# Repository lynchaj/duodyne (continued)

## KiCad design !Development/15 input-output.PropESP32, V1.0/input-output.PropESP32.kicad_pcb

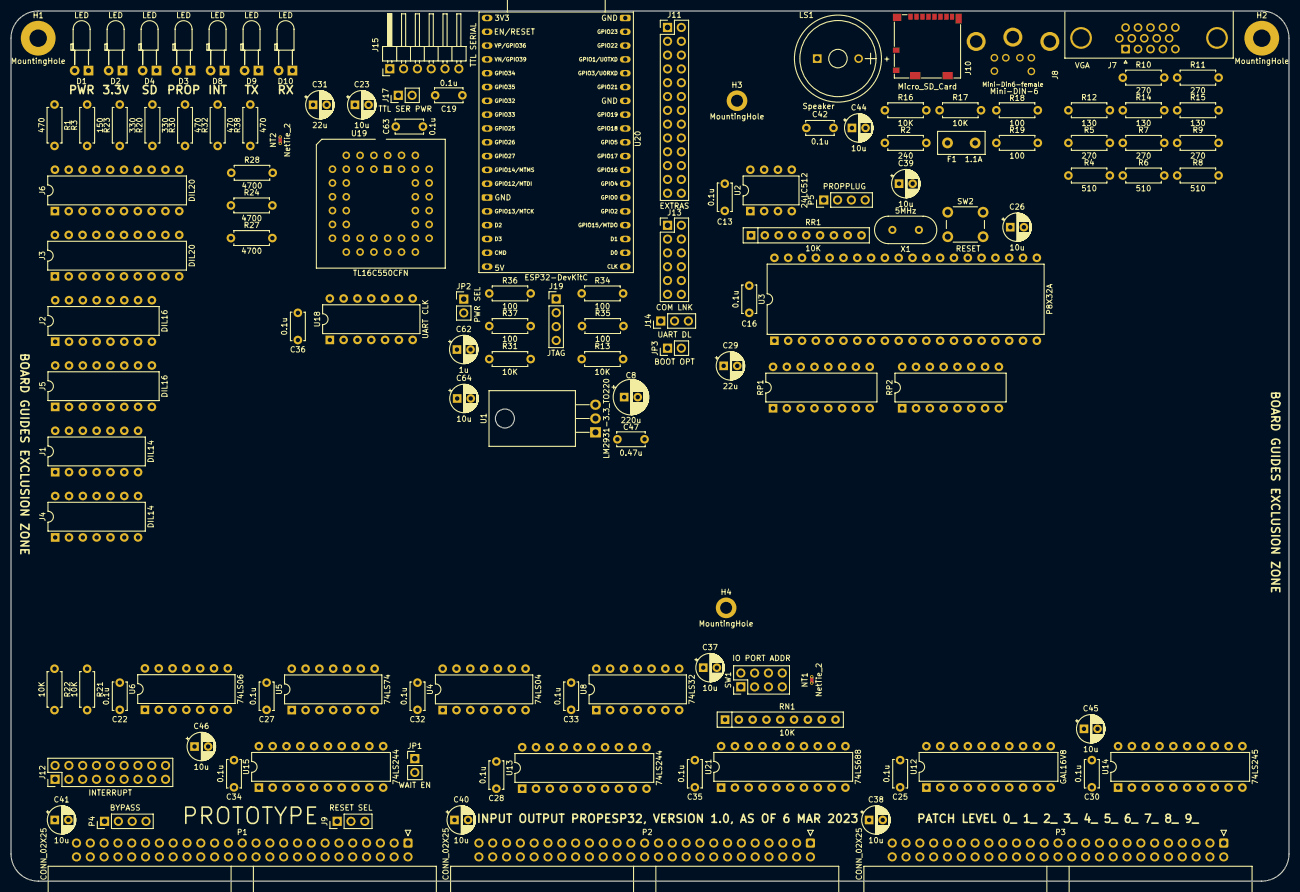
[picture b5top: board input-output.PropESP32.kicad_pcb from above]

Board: 2 copper layers, 235.0 x 160.0 mm, 127 parts (0 on the bottom side), 192 nets, no tracks yet.

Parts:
C8: 220u; CP_Radial_D6.3mm_P2.50mm
C13, C16, C19, C22, C25, C27, C28, C30, C32, C33, C34, C35, C36, C42, C63: 0.1u; C_Disc_D5.0mm_W2.5mm_P5.00mm
C23, C26, C37, C38, C39, C40, C41, C44, C45, C46, C64: 10u; CP_Radial_D5.0mm_P2.50mm
C29, C31: 22u; CP_Radial_D5.0mm_P2.50mm
C47: 0.47u; C_Disc_D5.0mm_W2.5mm_P5.00mm
C62: 1u; CP_Radial_D5.0mm_P2.50mm
D1, D2, D3, D4, D8, D9, D10: LED; LED_D3.0mm_Horizontal_O3.81mm_Z2.0mm
F1: 1.1A; Fuse_Littelfuse_395Series
H1, H2: MountingHole; MountingHole_3.2mm_M3_Pad
H3, H4: MountingHole; MountingHole_2.2mm_M2_DIN965_Pad
J1, J4: DIL14; DIP-14_W7.62mm
J2, J5: DIL16; DIP-16_W7.62mm
J3, J6: DIL20; DIP-20_W7.62mm
J7: VGA; DSUB-15-HD_Female_Horizontal_P2.29x1.98mm_EdgePinOffset3.03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
J8: Mini-DIN-6; mini-din6-female
J9: RESET SEL; PinHeader_1x03_P2.54mm_Vertical
J10: Micro_SD_Card; microSD_HC_Molex_104031-0811
J11: EXTRAS; PinHeader_2x13_P2.54mm_Vertical
J12: INTERRUPT; PinHeader_2x09_P2.54mm_Vertical
J13: COM LNK; PinHeader_2x06_P2.54mm_Vertical
J14: UART DL; PinHeader_1x03_P2.54mm_Vertical
J15: TTL SERIAL; PinHeader_1x06_P2.54mm_Horizontal
J17: TTL SER PWR; PinHeader_1x02_P2.54mm_Vertical
J19: JTAG; PinHeader_1x04_P2.54mm_Vertical
JP1: WAIT EN; PinHeader_1x02_P2.54mm_Vertical
JP2: PWR SEL; PinHeader_1x02_P2.54mm_Vertical
JP3: BOOT OPT; PinHeader_1x02_P2.54mm_Vertical
LS1: Speaker; MagneticBuzzer_StarMicronics_HMB-06_HMB-12
NT1, NT2: NetTie_2; NetTie-2_THT_Pad0.3mm
P1, P2, P3: CONN_02X25; IDC-Header_2x25_P2.54mm_Horizontal
P4: BYPASS; PinHeader_1x04_P2.54mm_Vertical
P5: PROPPLUG; PinHeader_1x04_P2.54mm_Vertical
R1, R30, R32, R38: 470; R_Axial_DIN0207_L6.3mm_D2.5mm_P7.62mm_Horizontal
R2: 240; R_Axial_DIN0207_L6.3mm_D2.5mm_P7.62mm_Horizontal
R3: 150; R_Axial_DIN0207_L6.3mm_D2.5mm_P7.62mm_Horizontal
R4, R6, R8: 510; R_Axial_DIN0207_L6.3mm_D2.5mm_P7.62mm_Horizontal
R5, R7, R9, R10, R11: 270; R_Axial_DIN0207_L6.3mm_D2.5mm_P7.62mm_Horizontal
R12, R14, R15: 130; R_Axial_DIN0207_L6.3mm_D2.5mm_P7.62mm_Horizontal
R13, R16, R17, R21, R22, R31: 10K; R_Axial_DIN0207_L6.3mm_D2.5mm_P7.62mm_Horizontal
R18, R19, R34, R35, R36, R37: 100; R_Axial_DIN0207_L6.3mm_D2.5mm_P7.62mm_Horizontal
R20, R23: 330; R_Axial_DIN0207_L6.3mm_D2.5mm_P7.62mm_Horizontal
R24, R27, R28: 4700; R_Axial_DIN0207_L6.3mm_D2.5mm_P7.62mm_Horizontal
RN1: 10K; R_Array_SIP9
RP1, RP2: 4700; DIP-16_W7.62mm
RR1: 10K; R_Array_SIP9
SW1: IO PORT ADDR; PinHeader_2x04_P2.54mm_Vertical
SW2: RESET; SW_PUSH_6mm
U1: LM2931-3.3_TO220; TO-220-3_Horizontal_TabDown
U2: 24LC512; DIP-8_W7.62mm
U3: P8X32A; DIP-40_W15.24mm
U4: 74LS04; DIP-14_W7.62mm
U5: 74LS74; DIP-14_W7.62mm
U6: 74LS06; DIP-14_W7.62mm
U8: 74LS32; DIP-14_W7.62mm
U12: GAL16V8; DIP-20_W7.62mm
U13, U15: 74LS244; DIP-20_W7.62mm
U14: 74LS245; DIP-20_W7.62mm
U18: UART CLK; DIP-14_W7.62mm
U19: TL16C550CFN; PLCC-44_THT-Socket
U20: ESP32-DevKitC
U21: 74LS688; DIP-20_W7.62mm
X1: 5MHz; Crystal_HC49-4H_Vertical

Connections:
+12V: P2.19, P2.20
-12V: P2.37, P2.38
/ESP32/CLK-ESP32: J11.22, U20.20 (SD_CLK/GPIO6)
/ESP32/CLK_UART: U18.8, U18.11, U19.18 (XIN)
/ESP32/CMD: J11.24, U20.18 (CMD)
/ESP32/EN: C62.1, R31.1, U20.2 (CHIP_PU)
/ESP32/INT: U6.9, U6.11, U19.33 (INTR)
/ESP32/IO0: JP3.1 (A), U20.25 (*GPIO0/BOOT/ADC2_CH1)
/ESP32/IO2: J11.16, U20.24 (ADC2_CH2/*GPIO2)
/ESP32/IO4: J13.2, U20.26 (ADC2_CH0/GPIO4)
/ESP32/IO5: J13.4, U20.29 (*GPIO5)
/ESP32/IO16: J11.14, U20.27 (GPIO16)
/ESP32/IO17: J11.12, U20.28 (GPIO17)
/ESP32/IO18: J13.6, U20.30 (GPIO18)
/ESP32/IO19: J13.8, U20.31 (GPIO19)
/ESP32/IO21: J11.8, U20.33 (GPIO21)
/ESP32/IO22: J11.6, U20.36 (GPIO22)
/ESP32/IO23: J11.4, U20.37 (GPIO23)
/ESP32/IO25: J11.15, U20.9 (DAC_1/ADC2_CH8/GPIO25)
/ESP32/IO26: J11.17, U20.10 (DAC_2/ADC2_CH9/GPIO26)
/ESP32/IO27: J11.19, U20.11 (ADC2_CH7/GPIO27)
/ESP32/IO32: J11.11, U20.7 (32K_XP/GPIO32/ADC1_CH4)
/ESP32/IO33: J11.13, U20.8 (32K_XN/GPIO33/ADC1_CH5)
/ESP32/IO34: J11.7, U20.5 (VDET_1/GPIO34/ADC1_CH6)
/ESP32/IO35: J11.9, U20.6 (VDET_2/GPIO35/ADC1_CH7)
/ESP32/MTCK: R37.1, U20.15 (MTCK/GPIO13/ADC2_CH4)
/ESP32/MTDI: R34.1, U20.13 (*MTDI/GPIO12/ADC2_CH5)
/ESP32/MTDO: R35.1, U20.23 (*MTDO/GPIO15/ADC2_CH3)
/ESP32/MTMS: R36.1, U20.12 (MTMS/GPIO14/ADC2_CH6)
/ESP32/RXD: J13.12, J14.2, U20.34 (U0RXD/GPIO3)
/ESP32/SD0: J11.20, U20.21 (SD_DATA0/GPIO7)
/ESP32/SD1: J11.18, U20.22 (SD_DATA1/GPIO8)
/ESP32/SD2: J11.23, U20.16 (SD_DATA2/GPIO9)
/ESP32/SD3: J11.25, U20.17 (SD_DATA3/GPIO10)
/ESP32/SENSOR_VN: J11.5, U20.4 (SENSOR_VN/GPIO39/ADC1_CH3)
/ESP32/SENSOR_VP: J11.3, U20.3 (SENSOR_VP/GPIO36/ADC1_CH0)
/ESP32/TTL_CTS#: J13.5, J15.6, U19.40 (~CTS)
/ESP32/TTL_RTS#: J13.7, J15.2, U19.36 (~RTS)
/ESP32/TTL_RX: J13.1, J13.9, J15.4, U8.12, U8.13, U19.11 (SIN)
/ESP32/TTL_TX: J13.3, J13.11, J15.5, U8.9, U8.10, U19.13 (SOUT)
/ESP32/TXD: J13.10, J14.3, U20.35 (U0TXD/GPIO1)
/ESP32/VCC_ESP32: JP2.2 (B), U20.19 (5V)
/ESP32/bRESET: R28.1, U4.8
/ESP32/pRESET: R28.2, U19.39 (MR)
/Propeller/BLUE: J7.3, R8.2, R9.2, R15.2
/Propeller/CLR: R13.2, U3.17 (P12), U4.3
/Propeller/DAT2: J10.1 (DAT2), R17.2
/Propeller/DI/CMD: J10.3 (CMD), RR1.5 (R4), U3.35 (P26)
/Propeller/DO/DAT0: J10.7 (DAT0), RR1.7 (R6), U3.33 (P24)
/Propeller/GREEN: J7.2, R6.2, R7.2, R14.2
/Propeller/HSYNC: J7.13, R10.2
/Propeller/KBD_CLK: R19.1, RR1.9 (R8), U3.20 (P15)
/Propeller/KBD_DAT: R18.1, RR1.8 (R7), U3.19 (P14)
/Propeller/KBD_VCC: F1.2, J7.9, J8.4
/Propeller/RED: J7.1, R4.2, R5.2, R12.2
/Propeller/RX: P5.3, U3.40 (P31)
/Propeller/SCL: RR1.3 (R2), U2.6 (SCL), U3.37 (P28)
/Propeller/SDA: RR1.2 (R1), U2.5 (SDA), U3.38 (P29)
/Propeller/SDCLK: J10.5 (CLK), RR1.6 (R5), U3.34 (P25)
/Propeller/SPK: R2.2, U3.18 (P13)
/Propeller/TX: P5.4, U3.39 (P30)
/Propeller/VSYNC: J7.14, R11.2
/Propeller/nIRQ/DAT1: J10.8 (DAT1), R16.2
/Propeller/~nCS/DAT3: J10.2 (DAT3/CD), RR1.4 (R3), U3.36 (P27), U6.3
A0: P2.35, U13.2 (I0a)
A1: P2.33, U13.4 (I1a)
A2: P2.31, U13.6 (I2a)
A3: P2.29, U13.8 (I3a)
A4: P2.27, U13.11 (I0b)
A5: P2.25, U13.13 (I1b)
A6: P2.23, U13.15 (I2b)
A7: P2.21, U13.17 (I3b)
D0: P3.33, U14.2 (A0)
D1: P3.31, U14.3 (A1)
D2: P3.29, U14.4 (A2)
D3: P3.27, U14.5 (A3)
D4: P3.25, U14.6 (A4)
D5: P3.23, U14.7 (A5)
D6: P3.21, U14.8 (A6)
D7: P3.19, U14.9 (A7)
GND: C8.2, C13.2, C16.2, C19.2, C22.2, C23.2, C25.2, C26.2, C27.2, C28.2, C29.2, C30.2, C31.2, C32.2, C33.2, C34.2, C35.2, C36.2, C37.2, C38.2, C39.2, C40.2, C41.2, C42.2, C45.2, C46.2, C47.2, C62.2, C63.2, C64.2, D1.1 (K), D2.1 (K), H1.1, H2.1, J7.0, J7.5, J7.6, J7.7, J7.8, J7.10, J8.3, J10.6 (VSS), J10.9 (SHIELD), J11.2, J11.10, J11.21, J14.1, J15.1, JP3.2 (B), LS1.1, NT1.1, P1.49, P1.50, P2.49, P2.50, P3.49, P3.50, P5.1, R12.1, R14.1, R15.1, SW2.1, U1.2 (GND), U2.1 (A0), U2.2 (A1), U2.3 (A2), U2.4 (GND), U2.7 (WP), U3.9 (VSS), U3.10 (BOEn), U3.29 (VSS), U4.7 (GND), U5.7 (GND), U6.7 (GND), U8.7 (GND), U12.10 (GND), U13.10 (GND), U14.10 (GND), U15.10 (GND), U18.4, U18.7, U19.22 (GND), U20.14 (GND), U20.32 (GND), U20.38 (GND), U21.10 (GND)
unnamed: C42.1, C44.1, R2.1
unnamed: C44.2, LS1.2
unnamed: D1.2 (A), R1.1
unnamed: D2.2 (A), R3.2
unnamed: D3.1 (K), R20.2
unnamed: D4.1 (K), U6.6
unnamed: D4.2 (A), R23.2
unnamed: D8.1 (K), U6.10
unnamed: D8.2 (A), R30.2
unnamed: D9.1 (K), U8.8
unnamed: D9.2 (A), R32.2
unnamed: D10.1 (K), U8.11
unnamed: D10.2 (A), R38.2
unnamed: J8.1, R18.2
unnamed: J8.5, R19.2
unnamed: J9.2, U15.2 (I0a)
unnamed: J12.1, J12.3, J12.5, J12.7, J12.9, J12.11, J12.13, J12.15, J12.17, U6.8
unnamed: J15.3, J17.2
unnamed: J19.1, R36.2
unnamed: J19.2, R34.2
unnamed: J19.3, R37.2
unnamed: J19.4, R35.2
unnamed: JP1.1 (A), R21.2, U6.2
unnamed: R4.1, U3.28 (P23)
unnamed: R5.1, U3.27 (P22)
unnamed: R6.1, U3.26 (P21)
unnamed: R7.1, U3.25 (P20)
unnamed: R8.1, U3.24 (P19)
unnamed: R9.1, U3.23 (P18)
unnamed: R10.1, U3.22 (P17)
unnamed: R11.1, U3.21 (P16)
unnamed: R20.1, U5.6 (~Q)
unnamed: R22.2, U6.4, U6.5
unnamed: R24.2, U19.14 (CS0), U19.15 (CS1)
unnamed: R27.2, U19.21 (WR), U19.25 (RD), U19.28 (~ADS)
unnamed: RN1.2 (R1), SW1.1, U21.18 (R7)
unnamed: RN1.3 (R2), SW1.3, U21.16 (R6)
unnamed: RN1.4 (R3), SW1.5, U21.14 (R5)
unnamed: RN1.5 (R4), SW1.7, U21.12 (R4)
unnamed: RN1.9 (R8), U21.3 (R0), U21.4 (P1), U21.5 (R1), U21.6 (P2), U21.7 (R2), U21.8 (P3), U21.9 (R3)
unnamed: U3.30 (X1), X1.1
unnamed: U3.31 (X0), X1.2
unnamed: U4.2, U5.3 (C)
unnamed: U4.4, U5.1 (~R)
unnamed: U4.6, U8.2
unnamed: U5.5 (Q), U6.1
unnamed: U19.10 (RCLK), U19.17 (~BAUDOUT)
ONE: NT2.2, R24.1
VCC: C22.1, C25.1, C27.1, C28.1, C29.1, C30.1, C31.1, C32.1, C33.1, C34.1, C35.1, C37.1, C38.1, C39.1, C40.1, C41.1, C45.1, C46.1, C47.1, D3.2 (A), F1.1, J11.26, J17.1, JP2.1 (A), NT2.1, P1.1, P1.2, P2.1, P2.2, P3.1, P3.2, R1.2, R21.1, R22.1, R23.1, R30.1, R32.1, R38.1, RN1.1 (common), U1.1 (VI), U4.14 (VCC), U5.2 (D), U5.4 (~S), U5.14 (VCC), U6.14 (VCC), U8.14 (VCC), U12.20 (VCC), U13.20 (VCC), U14.20 (VCC), U15.20 (VCC), U21.20 (VCC)
VDD: C8.1, C13.1, C16.1, C19.1, C23.1, C26.1, C36.1, C63.1, C64.1, J10.4 (VDD), J11.1, R3.1, R13.1, R16.1, R17.1, R31.2, RR1.1 (common), U1.3 (VO), U2.8 (VCC), U3.12 (VDD), U3.32 (VDD), U18.1, U18.14, U19.44 (VCC), U20.1 (3V3)
ZERO: NT1.2, R27.1, SW1.2, SW1.4, SW1.6, SW1.8, U13.1 (OEa), U13.19 (OEb), U15.1 (OEa), U15.19 (OEb)
bA0: RP2.3 (R3.1), U13.18 (O0a)
bA1: RP2.4 (R4.1), U13.16 (O1a)
bA2: RP2.5 (R5.1), U13.14 (O2a)
bA3: U4.5, U8.4, U13.12 (O3a)
bA4: U13.9 (O0b), U21.11 (P4)
bA5: U13.7 (O1b), U21.13 (P5)
bA6: U13.5 (O2b), U21.15 (P6)
bA7: U13.3 (O3b), U21.17 (P7)
bD0: RP1.1 (R1.1), U14.18 (B0)
bD1: RP1.2 (R2.1), U14.17 (B1)
bD2: RP1.3 (R3.1), U14.16 (B2)
bD3: RP1.4 (R4.1), U14.15 (B3)
bD4: RP1.5 (R5.1), U14.14 (B4)
bD5: RP1.6 (R6.1), U14.13 (B5)
bD6: RP1.7 (R7.1), U14.12 (B6)
bD7: RP1.8 (R8.1), U14.11 (B7)
pA0: RP2.14 (R3.2), U3.14 (P9), U19.31 (A0)
pA1: RP2.13 (R4.2), U3.15 (P10), U19.30 (A1)
pA2: RP2.12 (R5.2), U19.29 (A2)
pD0: RP1.16 (R1.2), U3.1 (P0), U19.2 (D0)
pD1: RP1.15 (R2.2), U3.2 (P1), U19.3 (D1)
pD2: RP1.14 (R3.2), U3.3 (P2), U19.4 (D2)
pD3: RP1.13 (R4.2), U3.4 (P3), U19.5 (D3)
pD4: RP1.12 (R5.2), U3.5 (P4), U19.6 (D4)
pD5: RP1.11 (R6.2), U3.6 (P5), U19.7 (D5)
pD6: RP1.10 (R7.2), U3.7 (P6), U19.8 (D6)
pD7: RP1.9 (R8.2), U3.8 (P7), U19.9 (D7)
~BAI: P1.40, P4.4
~BAO: P1.42, P4.3
~CS_BRD: U8.1, U8.5, U14.19 (CE), U21.19 (P=R)
~CS_PROP: RP2.1 (R1.1), U4.1, U8.3
~CS_SERIAL: RP2.2 (R2.1), U8.6
~EIRQ0: J12.4, P1.45
~EIRQ1: J12.6, P1.43
~EIRQ2: J12.8, P1.41
~EIRQ3: J12.10, P1.39
~EIRQ4: J12.12, P1.37
~EIRQ5: J12.14, P1.35
~EIRQ6: J12.16, P1.33
~EIRQ7: J12.18, P1.31
~IEI: P1.44, P4.2
~IEO: P1.46, P4.1
~INT0: J12.2, P1.17
~IORQ: P1.7, U15.11 (I0b)
~M1: P1.11, U15.13 (I1b)
~RD: P1.3, U14.1 (A->B), U15.17 (I3b)
~RES_IN: J9.1, P1.20
~RES_OUT: J9.3, P1.21
~WAIT: JP1.2 (B), P1.25
~WR: P1.5, U15.15 (I2b)
~bIORQ: U15.9 (O0b), U21.1 (G)
~bM1: U15.7 (O1b), U21.2 (P0)
~bRD: RP2.6 (R6.1), U15.3 (O3b)
~bRESET: RP2.8 (R8.1), U4.9, U15.18 (O0a)
~bWR: RP2.7 (R7.1), U15.5 (O2b)
~pCS_PROP: RP2.16 (R1.2), U3.13 (P8)
~pCS_SERIAL: RP2.15 (R2.2), U19.16 (~CS2)
~pRD: RP2.11 (R6.2), U3.16 (P11), U19.24 (~RD)
~pRESET: P5.2, RP2.9 (R8.2), SW2.2, U3.11 (RESn)
~pWR: RP2.10 (R7.2), U19.20 (~WR)

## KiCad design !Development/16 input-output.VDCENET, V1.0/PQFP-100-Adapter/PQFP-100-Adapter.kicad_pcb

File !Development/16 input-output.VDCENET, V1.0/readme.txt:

The VDCENET IO board provides MOSTEK 8568 VDC video and an RTL8019AS wired Ethernet interface

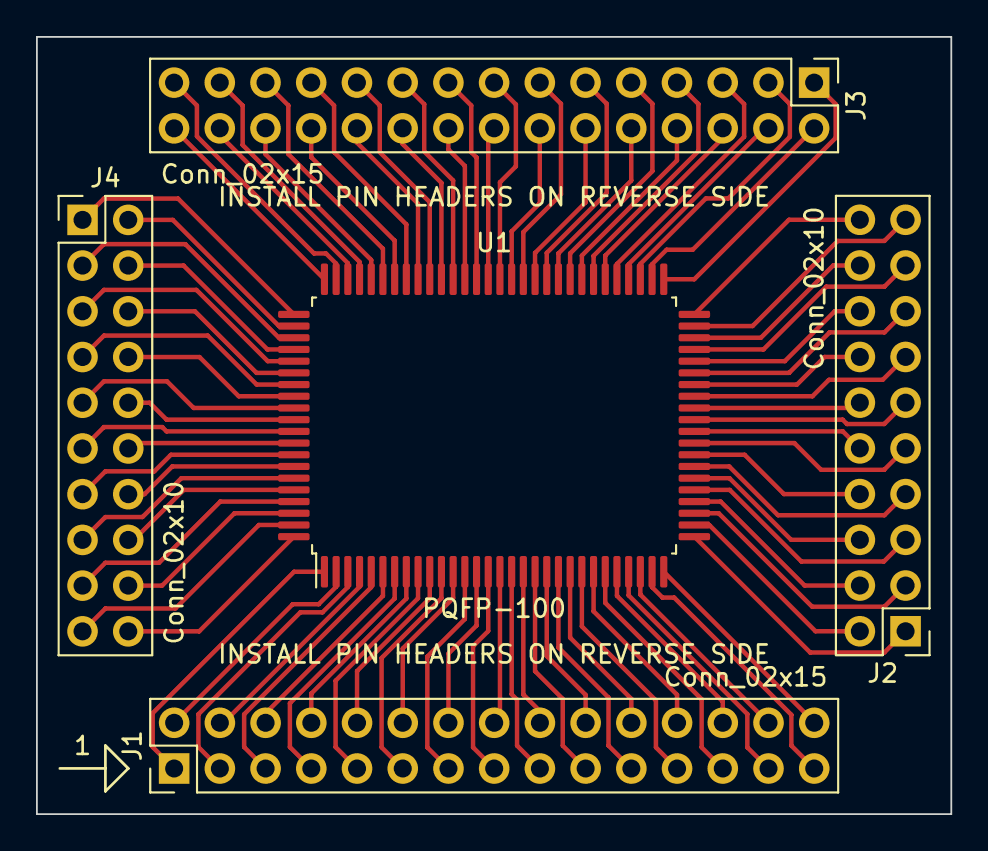
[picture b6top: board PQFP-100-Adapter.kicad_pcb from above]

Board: 2 copper layers, 50.8 x 43.2 mm, 5 parts (0 on the bottom side), 100 nets.

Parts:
J1, J3: Conn_02x15; PinHeader_2x15_P2.54mm_Vertical
J2, J4: Conn_02x10; PinHeader_2x10_P2.54mm_Vertical
U1: PQFP-100; PQFP-100_14x20mm_P0.65mm

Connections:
unnamed: J1.1, U1.1
unnamed: J1.2, U1.2
unnamed: J1.3, U1.3
unnamed: J1.4, U1.4
unnamed: J1.5, U1.5
unnamed: J1.6, U1.6
unnamed: J1.7, U1.7
unnamed: J1.8, U1.8
unnamed: J1.9, U1.9
unnamed: J1.10, U1.10
unnamed: J1.11, U1.11
unnamed: J1.12, U1.12
unnamed: J1.13, U1.13
unnamed: J1.14, U1.14
unnamed: J1.15, U1.15
unnamed: J1.16, U1.16
unnamed: J1.17, U1.17
unnamed: J1.18, U1.18
unnamed: J1.19, U1.19
unnamed: J1.20, U1.20
unnamed: J1.21, U1.21
unnamed: J1.22, U1.22
unnamed: J1.23, U1.23
unnamed: J1.24, U1.24
unnamed: J1.25, U1.25
unnamed: J1.26, U1.26
unnamed: J1.27, U1.27
unnamed: J1.28, U1.28
unnamed: J1.29, U1.29
unnamed: J1.30, U1.30
unnamed: J2.1, U1.31
unnamed: J2.2, U1.32
unnamed: J2.3, U1.33
unnamed: J2.4, U1.34
unnamed: J2.5, U1.35
unnamed: J2.6, U1.36
unnamed: J2.7, U1.37
unnamed: J2.8, U1.38
unnamed: J2.9, U1.39
unnamed: J2.10, U1.40
unnamed: J2.11, U1.41
unnamed: J2.12, U1.42
unnamed: J2.13, U1.43
unnamed: J2.14, U1.44
unnamed: J2.15, U1.45
unnamed: J2.16, U1.46
unnamed: J2.17, U1.47
unnamed: J2.18, U1.48
unnamed: J2.19, U1.49
unnamed: J2.20, U1.50
unnamed: J3.1, U1.51
unnamed: J3.2, U1.52
unnamed: J3.3, U1.53
unnamed: J3.4, U1.54
unnamed: J3.5, U1.55
unnamed: J3.6, U1.56
unnamed: J3.7, U1.57
unnamed: J3.8, U1.58
unnamed: J3.9, U1.59
unnamed: J3.10, U1.60
unnamed: J3.11, U1.61
unnamed: J3.12, U1.62
unnamed: J3.13, U1.63
unnamed: J3.14, U1.64
unnamed: J3.15, U1.65
unnamed: J3.16, U1.66
unnamed: J3.17, U1.67
unnamed: J3.18, U1.68
unnamed: J3.19, U1.69
unnamed: J3.20, U1.70
unnamed: J3.21, U1.71
unnamed: J3.22, U1.72
unnamed: J3.23, U1.73
unnamed: J3.24, U1.74
unnamed: J3.25, U1.75
unnamed: J3.26, U1.76
unnamed: J3.27, U1.77
unnamed: J3.28, U1.78
unnamed: J3.29, U1.79
unnamed: J3.30, U1.80
unnamed: J4.1, U1.81
unnamed: J4.2, U1.82
unnamed: J4.3, U1.83
unnamed: J4.4, U1.84
unnamed: J4.5, U1.85 (84)
unnamed: J4.6, U1.86
unnamed: J4.7, U1.87
unnamed: J4.8, U1.88
unnamed: J4.9, U1.89
unnamed: J4.10, U1.90
unnamed: J4.11, U1.91
unnamed: J4.12, U1.92
unnamed: J4.13, U1.93
unnamed: J4.14, U1.94
unnamed: J4.15, U1.95
unnamed: J4.16, U1.96
unnamed: J4.17, U1.97
unnamed: J4.18, U1.98
unnamed: J4.19, U1.99
unnamed: J4.20, U1.100

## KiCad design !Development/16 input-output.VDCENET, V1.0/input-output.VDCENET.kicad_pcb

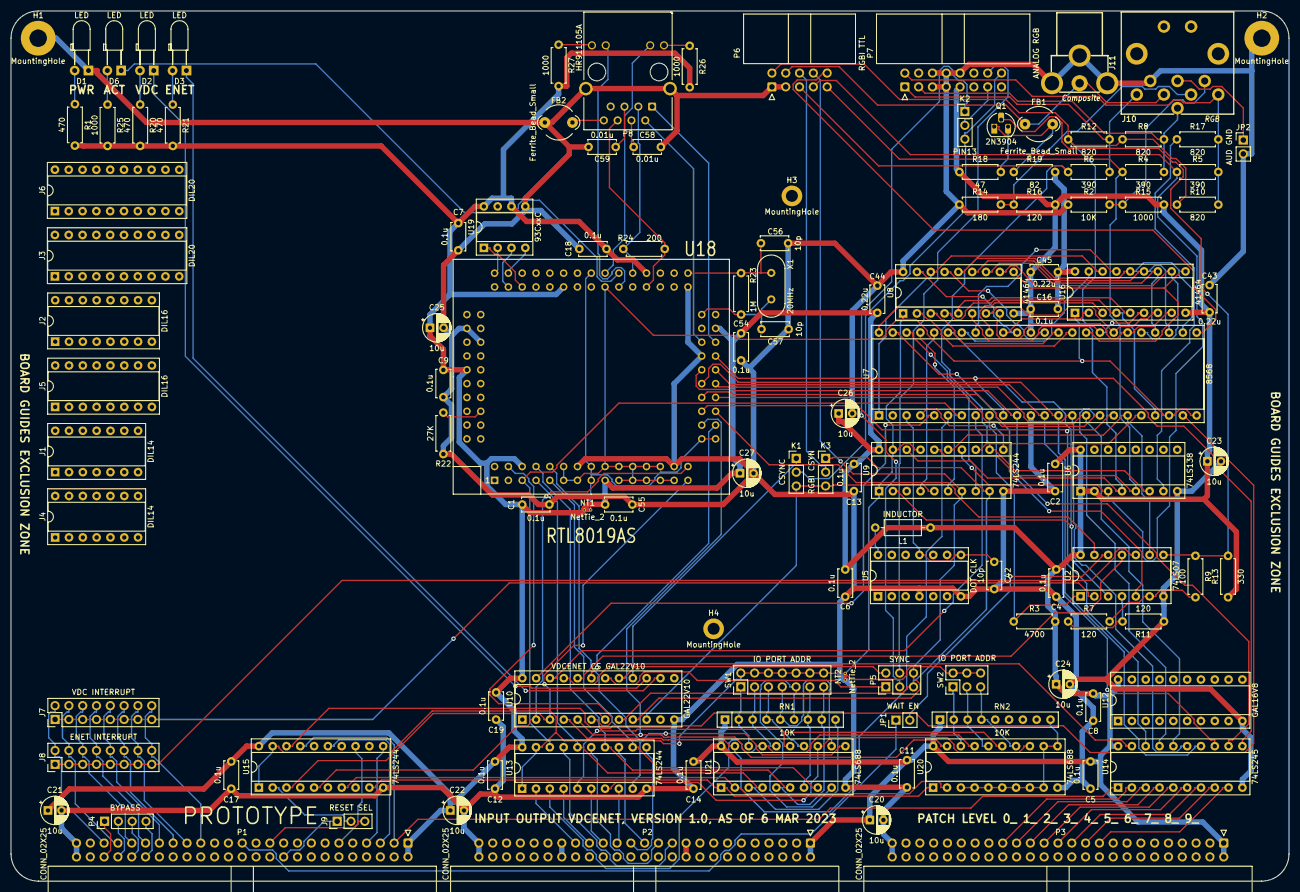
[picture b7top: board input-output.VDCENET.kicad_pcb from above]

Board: 2 copper layers, 235.0 x 160.0 mm, 120 parts (0 on the bottom side), 171 nets.

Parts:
C1, C2, C4, C5, C6, C7, C8, C9, C11, C12, C13, C14, C16, C17, C18, C19, C54, C55: 0.1u; C_Disc_D5.0mm_W2.5mm_P5.00mm
C20, C21, C22, C23, C24, C25, C26, C27: 10u; CP_Radial_D5.0mm_P2.50mm
C42, C56, C57: 10p; C_Disc_D5.0mm_W2.5mm_P5.00mm
C43, C44, C45: 0.22u; C_Disc_D5.0mm_W2.5mm_P5.00mm
C58, C59: 0.01u; C_Disc_D5.0mm_W2.5mm_P5.00mm
D1, D2, D3, D6: LED; LED_D3.0mm_Horizontal_O3.81mm_Z2.0mm
FB1, FB2: Ferrite_Bead_Small; LairdTech_28C0236-0JW-10
H1, H2: MountingHole; MountingHole_3.2mm_M3_Pad
H3, H4: MountingHole; MountingHole_2.2mm_M2_DIN965_Pad
J1, J4: DIL14; DIP-14_W7.62mm_Socket
J2, J5: DIL16; DIP-16_W7.62mm_Socket
J3, J6: DIL20; DIP-20_W7.62mm_Socket
J7: VDC INTERRUPT; PinHeader_2x08_P2.54mm_Vertical
J8: ENET INTERRUPT; PinHeader_2x08_P2.54mm_Vertical
J9: RESET SEL; PinHeader_1x03_P2.54mm_Vertical
J10: RGB; Conn_DIN_8pin
J11: Composite; Conn_RCA_Right
JP1: WAIT EN; PinHeader_1x02_P2.54mm_Vertical
JP2: AUD GND; PinHeader_1x02_P2.54mm_Vertical
K1: CSYNC; PinHeader_1x03_P2.54mm_Vertical
K2: PIN13; PinHeader_1x03_P2.54mm_Vertical
K3: RGBI CSYN; PinHeader_1x03_P2.54mm_Vertical
L1: INDUCTOR; L_Axial_L6.6mm_D2.7mm_P10.16mm_Horizontal_Vishay_IM-2
NT1, NT2: NetTie_2; NetTie-2_THT_Pad0.3mm
P1, P2, P3: CONN_02X25; IDC-Header_2x25_P2.54mm_Horizontal
P4: BYPASS; PinHeader_1x04_P2.54mm_Vertical
P5: SYNC; PinHeader_2x03_P2.54mm_Vertical
P6: RGBI TTL; IDC-Header_2x05_P2.54mm_Horizontal
P7: ANALOG RGB; IDC-Header_2x08_P2.54mm_Horizontal
P8: HR911105A; RJ45_Hanrun_HR911105A
Q1: 2N3904; TO-92L_HandSolder
R1, R20, R21: 470; R_Axial_DIN0207_L6.3mm_D2.5mm_P7.62mm_Horizontal
R2: 10K; R_Axial_DIN0207_L6.3mm_D2.5mm_P7.62mm_Horizontal
R3: 4700; R_Axial_DIN0207_L6.3mm_D2.5mm_P7.62mm_Horizontal
R4, R5, R6: 390; R_Axial_DIN0207_L6.3mm_D2.5mm_P7.62mm_Horizontal
R7, R11, R16: 120; R_Axial_DIN0207_L6.3mm_D2.5mm_P7.62mm_Horizontal
R8, R10, R12, R17: 820; R_Axial_DIN0207_L6.3mm_D2.5mm_P7.62mm_Horizontal
R9: 100; R_Axial_DIN0207_L6.3mm_D2.5mm_P7.62mm_Horizontal
R13: 330; R_Axial_DIN0207_L6.3mm_D2.5mm_P7.62mm_Horizontal
R14: 180; R_Axial_DIN0207_L6.3mm_D2.5mm_P7.62mm_Horizontal
R15, R25, R26, R27: 1000; R_Axial_DIN0207_L6.3mm_D2.5mm_P7.62mm_Horizontal
R18: 47; R_Axial_DIN0207_L6.3mm_D2.5mm_P7.62mm_Horizontal
R19: 82; R_Axial_DIN0207_L6.3mm_D2.5mm_P7.62mm_Horizontal
R22: 27K; R_Axial_DIN0207_L6.3mm_D2.5mm_P7.62mm_Horizontal
R23: 1M; R_Axial_DIN0207_L6.3mm_D2.5mm_P7.62mm_Horizontal
R24: 200; R_Axial_DIN0207_L6.3mm_D2.5mm_P7.62mm_Horizontal
RN1, RN2: 10K; R_Array_SIP9
SW1: IO PORT ADDR; PinHeader_2x07_P2.54mm_Vertical
SW2: IO PORT ADDR; PinHeader_2x03_P2.54mm_Vertical
U2: 74LS07; DIP-14_W7.62mm_Socket
U5: DOT CLK; DIP-14_W7.62mm_Socket
U6: 74LS138; DIP-16_W7.62mm_Socket
U7: 8568; DIP-48_W15.24mm_Socket
U8, U16: 41464; DIP-18_W7.62mm_Socket
U9, U13, U15: 74LS244; DIP-20_W7.62mm_Socket
U10: GAL22V10; DIP-24_W7.62mm_Socket
U12: GAL16V8; DIP-20_W7.62mm_Socket
U14: 74LS245; DIP-20_W7.62mm_Socket
U18: RTL8019AS; QFP100-DIP-Adapter
U19: 93CxxC; DIP-8_W7.62mm_Socket
U20, U21: 74LS688; DIP-20_W7.62mm_Socket
X1: 20MHz; Crystal_HC49-4H_Vertical

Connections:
+12V: P2.19, P2.20
-12V: P2.37, P2.38
/VDC/AUDIO: J10.2, JP2.1 (A)
/VDC/AV: J10.3, R2.2, R15.1
/VDC/B: U7.44 (B), U9.4 (I1a)
/VDC/BOUT: P6.9, R4.1, U6.5 (E2), U9.16 (O1a)
/VDC/CAS#: U7.1 (~CAS), U8.16 (~CAS), U16.16 (~CAS)
/VDC/CSYNC: U2.9, U7.19 (CSYNC), U9.15 (I2b)
/VDC/CV: U2.5, U7.47 (COMPVIDEO)
/VDC/CVBS: FB1.1, J10.4, J11.1 (In), P6.4
/VDC/DA0: U7.26 (DA0), U8.14 (A0), U16.14 (A0)
/VDC/DA1: U7.27 (DA1), U8.13 (A1), U16.13 (A1)
/VDC/DA2: U7.28 (DA2), U8.12 (A2), U16.12 (A2)
/VDC/DA3: U7.29 (DA3), U8.11 (A3), U16.11 (A3)
/VDC/DA4: U7.30 (DA4), U8.8 (A4), U16.8 (A4)
/VDC/DA5: U7.31 (DA5), U8.7 (A5), U16.7 (A5)
/VDC/DA6: U7.32 (DA6), U8.6 (A6), U16.6 (A6)
/VDC/DA7: U7.33 (DA7), U8.10 (A7), U16.10 (A7)
/VDC/DCLK#: C42.1, U5.8, U5.11, U7.3 (~DCLK)
/VDC/DD0: U7.34 (DD0), U8.2 (D0)
/VDC/DD1: U7.35 (DD1), U8.3 (D1)
/VDC/DD2: U7.36 (DD2), U8.15 (D2)
/VDC/DD3: U7.38 (DD3), U8.17 (D3)
/VDC/DD4: U7.39 (DD4), U16.2 (D0)
/VDC/DD5: U7.40 (DD5), U16.3 (D1)
/VDC/DD6: U7.41 (DD6), U16.15 (D2)
/VDC/DD7: U7.42 (DD7), U16.17 (D3)
/VDC/DR-W: U7.21 (DR/~W), U8.4 (~W), U16.4 (~W)
/VDC/FIX_BROWN: R17.1, U6.7 (O7)
/VDC/G: U7.45 (G), U9.6 (I2a)
/VDC/GOUT: P6.7, R5.1, U6.3 (A2), U9.14 (O2a)
/VDC/HSYN: U7.4 (HSYNC), U9.11 (I0b)
/VDC/I: U2.3, U7.43 (I), U9.2 (I0a)
/VDC/INTR#: R3.1, U2.1, U7.9 (INTR)
/VDC/IOUT: P6.2, R8.1, R10.1, R12.1, U6.4 (E1), U9.18 (O0a)
/VDC/LP2#: P6.10, U7.25 (LPEN)
/VDC/MONOCHROME: FB1.2, Q1.1 (E), R19.1
/VDC/R: U7.46 (R), U9.8 (I3a)
/VDC/RAS#: U7.48 (~RAS), U8.5 (~RAS), U16.5 (~RAS)
/VDC/ROUT: P6.5, R6.1, U6.6 (E3), U9.12 (O3a)
/VDC/VGA-BLUE: J10.8, P7.3, R4.2, R8.2
/VDC/VGA-CSYNC: K1.2, K2.3, P7.16
/VDC/VGA-GREEN: J10.7, P7.2, R5.2, R10.2, R17.2
/VDC/VGA-HSYNC: K2.1, P5.3
/VDC/VGA-RED: J10.6, P7.1, R6.2, R12.2
/VDC/VGA-VSYNC: P5.4, P7.14
/VDC/VSYN: U7.20 (VSYNC), U9.13 (I1b)
/VDC/YS: J10.5, R14.2, R16.1
A0: P2.35, U13.2 (I0a)
A1: P2.33, U13.4 (I1a)
A2: P2.31, U13.6 (I2a)
A3: P2.29, U13.8 (I3a)
A4: P2.27, U13.11 (I0b)
A5: P2.25, U13.13 (I1b)
A6: P2.23, U13.15 (I2b)
A7: P2.21, U13.17 (I3b)
CSYNOUT: K1.3, K3.3, U9.5 (O2b), U10.10 (I9)
CS_VDC: U7.5 (CS), U10.23 (O0)
D0: P3.33, U14.2 (A0)
D1: P3.31, U14.3 (A1)
D2: P3.29, U14.4 (A2)
D3: P3.27, U14.5 (A3)
D4: P3.25, U14.6 (A4)
D5: P3.23, U14.7 (A5)
D6: P3.21, U14.8 (A6)
D7: P3.19, U14.9 (A7)
ENET_INT0: U10.6 (I5), U18.4 (INT0)
GND: C1.2, C2.2, C4.2, C5.2, C6.2, C7.2, C8.2, C9.2, C11.2, C12.2, C13.2, C14.2, C16.2, C17.2, C18.2, C19.2, C20.2, C21.2, C22.2, C23.2, C24.2, C25.2, C26.2, C27.2, C42.2, C43.2, C44.2, C45.2, C54.2, C55.2, C56.1, C57.1, C58.2, C59.2, D1.1 (K), FB2.1, H1.1, H2.1, J10.1, J11.2 (Ext), JP2.2 (B), NT2.1, P1.49, P1.50, P2.49, P2.50, P3.49, P3.50, P6.1, P6.3, P7.5, P7.6, P7.7, P7.8, P7.10, P8.SH (Shell), R2.1, R11.1, R14.1, R19.2, R22.2, U2.7 (GND), U5.4, U5.7, U6.8 (GND), U7.12 (GND), U8.18 (GND), U9.10 (GND), U10.12 (GND), U12.10 (GND), U13.10 (GND), U14.10 (GND), U15.10 (GND), U16.18 (GND), U18.14 (GND), U18.28 (GND), U18.44 (GND), U18.52 (GND), U18.83 (GND), U18.86 (GND), U19.5 (GND), U20.10 (GND), U21.10 (GND)
HSYNOUT: K3.1, P5.5, U9.9 (O0b), U10.8 (I7)
unnamed: C56.2, R23.1, U18.51 (X2), X1.1
unnamed: C57.2, R23.2, U18.50 (X1), X1.2
unnamed: C58.1, P8.4
unnamed: C59.1, P8.5
unnamed: D1.2 (A), R1.1
unnamed: D2.2 (A), R20.1
unnamed: D3.2 (A), R21.1
unnamed: D6.1 (K), U18.61 (LED0)
unnamed: D6.2 (A), R25.1
unnamed: FB2.2, P8.8 (GND)
unnamed: J7.1, J7.3, J7.5, J7.7, J7.9, J7.11, J7.13, J7.15, U2.2
unnamed: J8.1, J8.3, J8.5, J8.7, J8.9, J8.11, J8.13, J8.15, U2.10
unnamed: J9.2, U15.2 (I0a)
unnamed: JP1.2 (B), U2.12
unnamed: K2.2, P7.13
unnamed: K3.2, P6.6
unnamed: L1.2, U5.14
unnamed: P8.1 (TD+), U18.45 (TPOUT+)
unnamed: P8.2 (TD-), U18.46 (TPOUT-)
unnamed: P8.3 (RD+), R24.1, U18.59 (TPIN+)
unnamed: P8.6 (RD-), R24.2, U18.58 (TPIN-)
unnamed: P8.9 (LED_GREEN_P), R26.1
unnamed: P8.10 (LED_GREEN_M), U18.63 (LED2)
unnamed: P8.11 (LED_YELLOW_M), U18.62 (LED1)
unnamed: P8.12 (LED_YELLOW_P), R27.1
unnamed: Q1.2 (B), R9.1, R13.2, U2.8
unnamed: Q1.3 (C), R18.2
unnamed: R7.2, R9.2, U2.6
unnamed: R7.1, R11.2, U2.4
unnamed: R22.1, U18.96 (IOCS16B)
unnamed: RN1.2 (R1), SW1.1, U21.18 (R7)
unnamed: RN1.3 (R2), SW1.3, U21.16 (R6)
unnamed: RN1.4 (R3), SW1.5, U21.14 (R5)
unnamed: RN1.5 (R4), SW1.7, U21.12 (R4)
unnamed: RN1.6 (R5), SW1.9, U21.9 (R3)
unnamed: RN1.7 (R6), SW1.11, U21.7 (R2)
unnamed: RN1.8 (R7), SW1.13, U21.5 (R1)
unnamed: RN1.9 (R8), U21.3 (R0)
unnamed: RN2.2 (R1), SW2.1, U20.18 (R7)
unnamed: RN2.3 (R2), SW2.3, U20.16 (R6)
unnamed: RN2.4 (R3), SW2.5, U20.14 (R5)
unnamed: RN2.9 (R8), U20.3 (R0), U20.4 (P1), U20.5 (R1), U20.6 (P2), U20.7 (R2), U20.8 (P3), U20.9 (R3), U20.11 (P4), U20.12 (R4)
unnamed: U2.13, U18.35 (IOCHRDY)
unnamed: U18.76 (EECS), U19.1 (CS)
unnamed: U18.77 (EEDO), U19.4 (DO)
unnamed: U18.78 (EEDI), U19.3 (DI)
unnamed: U18.79 (EESK), U19.2 (SCLK)
ONE: NT1.2, U18.15 (A8), U18.16 (A9), U18.31 (SMEMRB), U18.32 (SMEMWB), U18.65 (JP)
RD: U7.8 (R/~W), U10.22 (O1)
VCC: C1.1, C2.1, C4.1, C5.1, C6.1, C7.1, C8.1, C9.1, C11.1, C12.1, C13.1, C14.1, C16.1, C17.1, C18.1, C19.1, C20.1, C21.1, C22.1, C23.1, C24.1, C25.1, C26.1, C27.1, C43.1, C44.1, C45.1, C54.1, C55.1, L1.1, NT1.1, P1.1, P1.2, P2.1, P2.2, P3.1, P3.2, P7.9, R1.2, R3.2, R13.1, R15.2, R16.2, R18.1, R20.2, R21.2, R25.2, R26.2, R27.2, RN1.1 (common), RN2.1 (common), U2.14 (VCC), U6.1 (A0), U6.2 (A1), U6.16 (VCC), U7.37 (VCC), U8.9 (VCC), U9.20 (VCC), U10.24 (VCC), U12.20 (VCC), U13.20 (VCC), U14.20 (VCC), U15.20 (VCC), U16.9 (VCC), U18.6 (VCC), U18.17 (VCC), U18.47 (VCC), U18.57 (VCC), U18.70 (VCC), U18.89 (VCC), U19.6 (ORG), U19.8 (VCC), U20.20 (VCC), U21.20 (VCC)
VSYNOUT: P5.6, P6.8, U9.7 (O1b), U10.9 (I8)
ZERO: NT2.2, SW1.2, SW1.4, SW1.6, SW1.8, SW1.10, SW1.12, SW1.14, SW2.2, SW2.4, SW2.6, U7.22 (INIT), U7.24 (TEST), U8.1 (~OE), U9.1 (OEa), U9.17 (I3b), U9.19 (OEb), U13.1 (OEa), U13.19 (OEb), U15.1 (OEa), U15.19 (OEb), U16.1 (~OE), U18.11 (A5), U18.12 (A6), U18.13 (A7), U18.18 (A10), U18.19 (A11), U18.20 (A12), U18.21 (A13), U18.22 (A14), U18.23 (A15), U18.24 (A16), U18.25 (A17), U18.26 (A18), U18.27 (A19), U18.64 (AUI)
bA0: U7.7 (~RS), U13.18 (O0a), U18.5 (A0)
bA1: U13.16 (O1a), U18.7 (A1), U21.4 (P1)
bA2: U13.14 (O2a), U18.8 (A2), U21.6 (P2)
bA3: U13.12 (O3a), U18.9 (A3), U21.8 (P3)
bA4: U13.9 (O0b), U18.10 (A4), U21.11 (P4)
bA5: U13.7 (O1b), U20.13 (P5), U21.13 (P5)
bA6: U13.5 (O2b), U20.15 (P6), U21.15 (P6)
bA7: U13.3 (O3b), U20.17 (P7), U21.17 (P7)
bD0: U7.18 (D0), U14.18 (B0), U18.36 (D0)
bD1: U7.17 (D1), U14.17 (B1), U18.37 (D1)
bD2: U7.16 (D2), U14.16 (B2), U18.38 (D2)
bD3: U7.15 (D3), U14.15 (B3), U18.39 (D3)
bD4: U7.14 (D4), U14.14 (B4), U18.40 (D4)
bD5: U7.13 (D5), U14.13 (B5), U18.41 (D5)
bD6: U7.11 (D6), U14.12 (B6), U18.42 (D6)
bD7: U7.10 (D7), U14.11 (B7), U18.43 (D7)
bRESET: U10.19 (O4), U18.33 (RSTDRV)
~BAI: P1.40, P4.4
~BAO: P1.42, P4.3
~BUS_EN: U10.21 (O2), U14.19 (CE)
~CSYNOUT: K1.1, U10.16 (O7)
~CS_ENET: U10.5 (I4), U18.34 (*AEN), U20.19 (P=R)
~CS_VDC: U7.6 (~CS), U10.4 (I3), U21.19 (P=R)
~EIRQ0: J7.2, J8.2, P1.45
~EIRQ1: J7.4, J8.4, P1.43
~EIRQ2: J7.6, J8.6, P1.41
~EIRQ3: J7.8, J8.8, P1.39
~EIRQ4: J7.10, J8.10, P1.37
~EIRQ5: J7.12, J8.12, P1.35
~EIRQ6: J7.14, J8.14, P1.33
~EIRQ7: J7.16, J8.16, P1.31
~ENET_INT0: U2.11, U10.20 (O3)
~ENET_LED: D3.1 (K), U10.14 (O9)
~HSYNOUT: P5.1, U10.18 (O5)
~IEI: P1.44, P4.2
~IEO: P1.46, P4.1
~IORQ: P1.7, U15.11 (I0b)
~M1: P1.11, U15.13 (I1b)
~RD: P1.3, U14.1 (A->B), U15.17 (I3b)
~RES_IN: J9.1, P1.20
~RES_OUT: J9.3, P1.21
~VDC_LED: D2.1 (K), U10.15 (O8)
~VSYNOUT: P5.2, U10.17 (O6)
~WAIT: JP1.1 (A), P1.25
~WR: P1.5, U15.15 (I2b)
~bIORQ: U15.9 (O0b), U20.1 (G), U21.1 (G)
~bM1: U15.7 (O1b), U20.2 (P0), U21.2 (P0)
~bRD: U10.3 (I2), U15.3 (O3b), U18.29 (*IORB)
~bRESET: U7.23 (~RES), U10.7 (I6), U15.18 (O0a)
~bWR: U10.2 (I1), U15.5 (O2b), U18.30 (*IOWB)
